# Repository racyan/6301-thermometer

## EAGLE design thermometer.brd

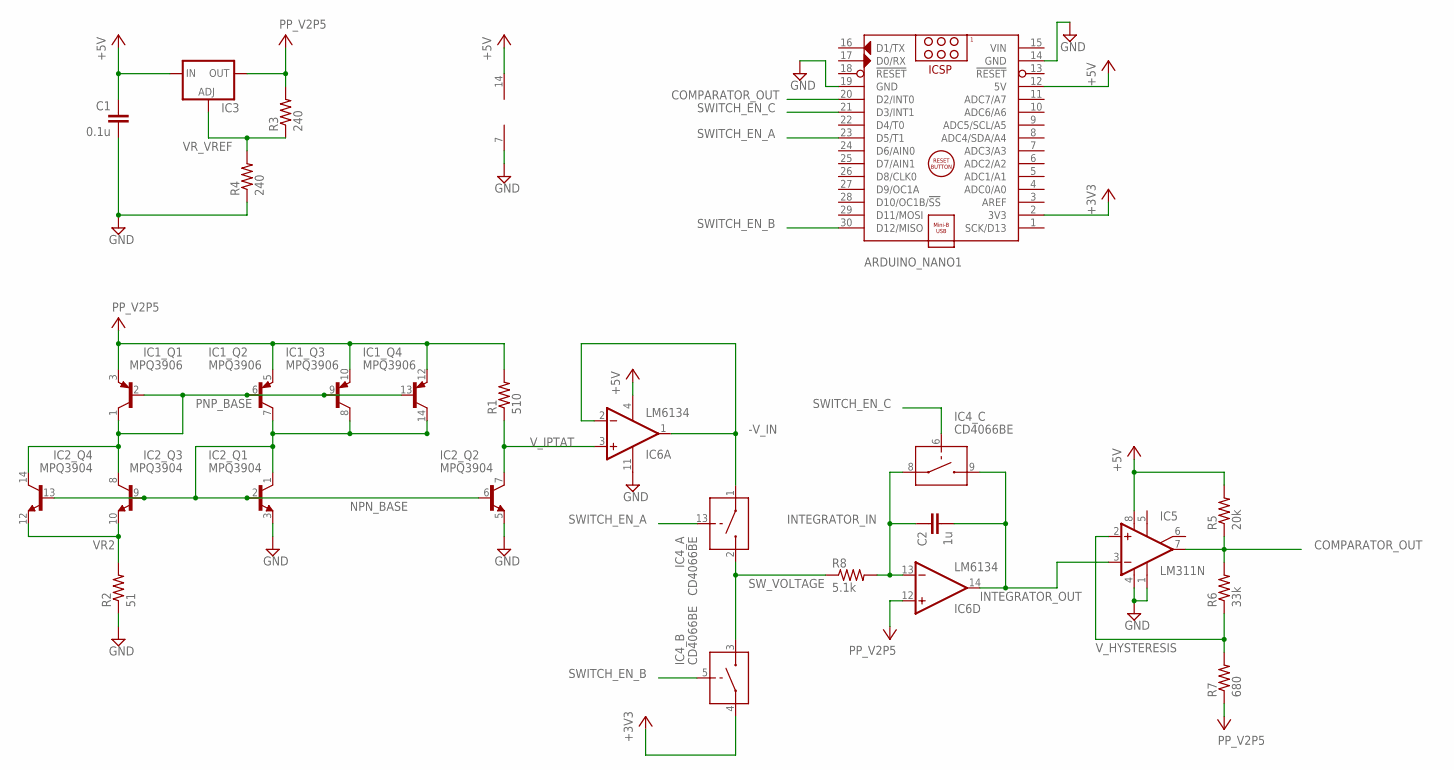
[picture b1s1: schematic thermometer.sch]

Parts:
ARDUINO_NANO1: ARDUINO_NANO
C1: 0.1u; C050-035X075
C2: 1u; C050-035X075
IC1: MPQ3906; DIL14
IC2: MPQ3904; DIL14
IC3: LM317TS; 317TS
IC4: CD4066BE; DIL14
IC5: LM311N; DIL08
IC6: LM6134; DIL14
R1: 510; 0207/10
R2: 51; 0207/10
R3, R4: 240; 0207/10
R5: 20k; 0207/10
R6: 33k; 0207/10
R7: 680; 0207/10
R8: 5.1k; 0207/10

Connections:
+3V3: ARDUINO_NANO1.2 (3V3), IC4.4 (IN/OUT1)
+5V: ARDUINO_NANO1.12 (5V), C1.1, IC3.3 (IN), IC4.14 (V+), IC5.8 (V+), IC6.4 (V+), R5.2
-V_IN: IC4.1 (IN/OUT1), IC6.1 (OUT), IC6.2 (-IN)
COMPARATOR_OUT: ARDUINO_NANO1.20 (D2/INT0), IC5.7 (OUT), R5.1, R6.2
GND: ARDUINO_NANO1.14 (GND), ARDUINO_NANO1.19 (GND), C1.2, IC2.3 (E), IC2.5 (E), IC4.7 (V-), IC5.1 (GND), IC5.4 (V-), IC6.11 (V-), R2.1, R4.1
INTEGRATOR_IN: C2.1, IC4.8 (IN/OUT1), IC6.13 (-IN), R8.2
INTEGRATOR_OUT: C2.2, IC4.9 (IN/OUT2), IC5.3 (-IN), IC6.14 (OUT)
NPN_BASE: IC1.7 (C), IC1.8 (C), IC1.14 (C), IC2.1 (C), IC2.2 (B), IC2.6 (B), IC2.9 (B), IC2.13 (B)
PNP_BASE: IC1.1 (C), IC1.2 (B), IC1.6 (B), IC1.9 (B), IC1.13 (B), IC2.8 (C), IC2.14 (C)
SWITCH_EN_A: ARDUINO_NANO1.23 (D5/T1), IC4.13 (CONTROL)
SWITCH_EN_B: ARDUINO_NANO1.30 (D12/MISO), IC4.5 (CONTROL)
SWITCH_EN_C: ARDUINO_NANO1.21 (D3/INT1), IC4.6 (CONTROL)
SW_VOLTAGE: IC4.2 (IN/OUT2), IC4.3 (IN/OUT2), R8.1
V+: IC1.3 (E), IC1.5 (E), IC1.10 (E), IC1.12 (E), IC3.2 (OUT), IC6.12 (+IN), R1.2, R3.2, R7.1
VIN: ARDUINO_NANO1.15 (VIN)
VR2: IC2.10 (E), IC2.12 (E), R2.2
VR_VREF: IC3.1 (ADJ), R3.1, R4.2
V_HYSTERESIS: IC5.2 (+IN), R6.1, R7.2
V_IPTAT: IC2.7 (C), IC6.3 (+IN), R1.1

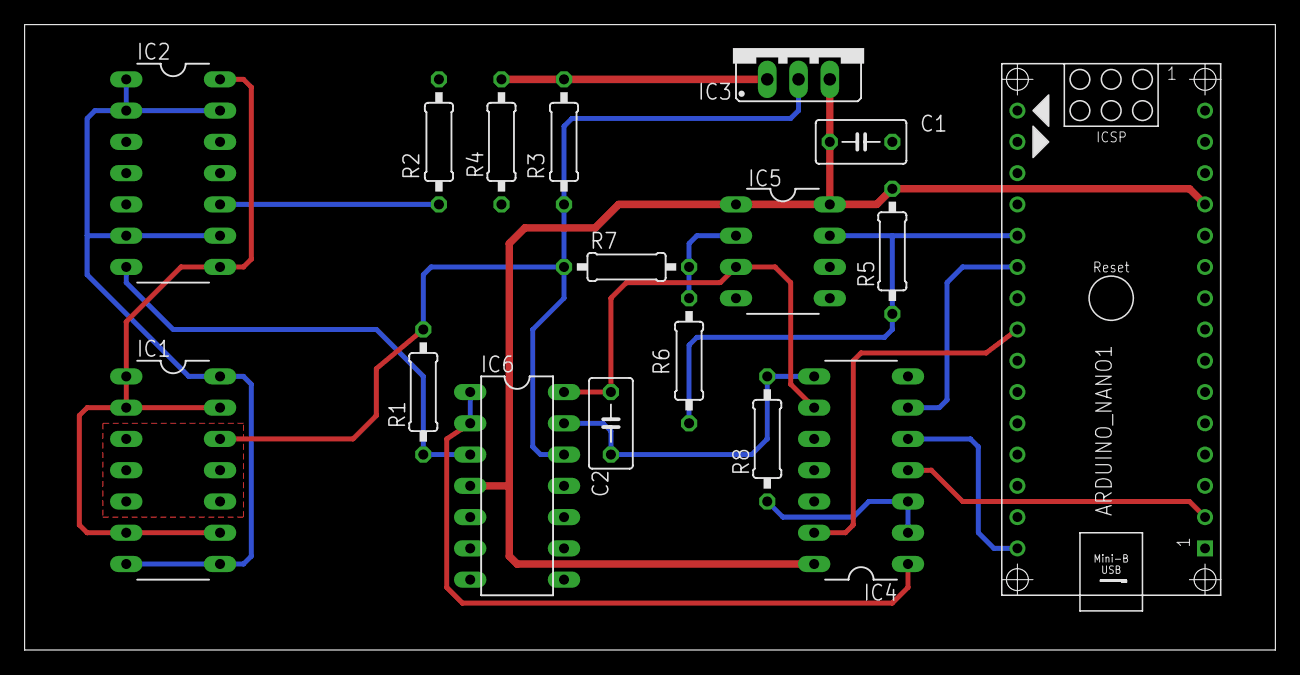
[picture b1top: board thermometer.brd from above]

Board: 2 copper layers, 101.6 x 50.8 mm, 17 parts (0 on the bottom side), 18 nets.

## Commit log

2016-12-05 :confetti_ball: Added .gitattributes & .gitignore files
2016-12-06 fixed in+ and in- pins of op amps and comparator
2016-12-13 fixed labelling
